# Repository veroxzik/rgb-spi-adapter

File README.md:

# rgb-spi-adapter
 Simple breakout board for the TLC59711 for use with rhythm game controllers.

## Current Release

v1.1 swaps the RGB headers around for compatibility with Yuancon controllers.

## Explanation
Designed for common anode RGBs. Individually wired works just fine too.

- Connectors are JST-XH 4 pin.
- Capacitors are 1uF 0805.
- Resistor is 0805, value per TLC59711 datasheet for your desired current.
- Solder jumper only if you're using 3.3V voltage across the board (LED and logic). Otherwise leave it open for 5V.

Use Adafruit TLC59711 library (get from Arduino library manager). It's plug and play!

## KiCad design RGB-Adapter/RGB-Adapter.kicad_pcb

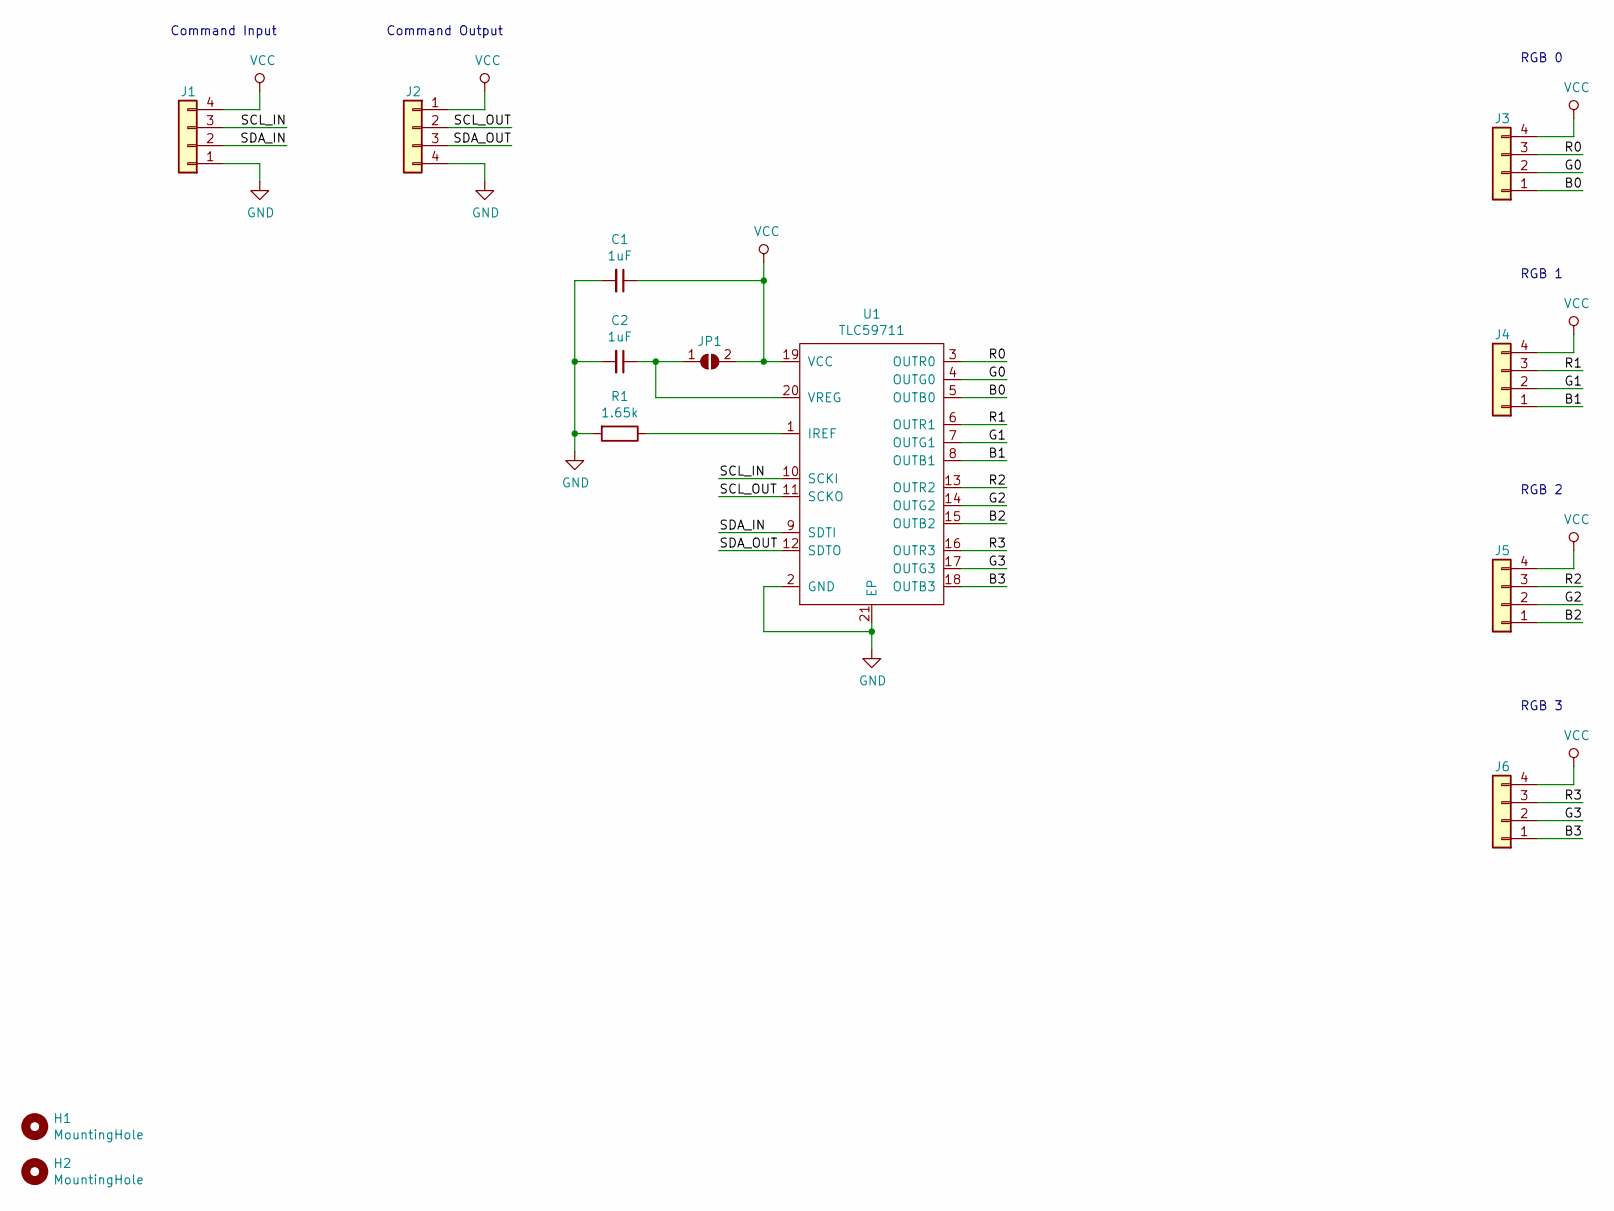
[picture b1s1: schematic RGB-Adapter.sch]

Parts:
C1, C2: 1uF; C_0603_1608Metric_Pad1.05x0.95mm_HandSolder
H1, H2: MountingHole; MountingHole_3.2mm_M3_DIN965
J1, J2, J3, J4, J5, J6: Conn_01x04; JST_XH_B4B-XH-A_1x04_P2.50mm_Vertical
JP1: SolderJumper_2_Open; SolderJumper-2_P1.3mm_Open_RoundedPad1.0x1.5mm
R1: 1.65k; R_0603_1608Metric_Pad1.05x0.95mm_HandSolder
U1: TLC59711; HTSSOP-20-1EP_4.4x6.5mm_P0.65mm_EP3.4x6.5mm_Mask2.75x3.43mm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

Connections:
/B0: J3.1, U1.5 (OUTB0)
/B1: J4.1, U1.8 (OUTB1)
/B2: J5.1, U1.15 (OUTB2)
/B3: J6.1, U1.18 (OUTB3)
/G0: J3.2, U1.4 (OUTG0)
/G1: J4.2, U1.7 (OUTG1)
/G2: J5.2, U1.14 (OUTG2)
/G3: J6.2, U1.17 (OUTG3)
/R0: J3.3, U1.3 (OUTR0)
/R1: J4.3, U1.6 (OUTR1)
/R2: J5.3, U1.13 (OUTR2)
/R3: J6.3, U1.16 (OUTR3)
/SCL_IN: J1.3, U1.10 (SCKI)
/SCL_OUT: J2.2, U1.11 (SCKO)
/SDA_IN: J1.2, U1.9 (SDTI)
/SDA_OUT: J2.3, U1.12 (SDTO)
GND: C1.2, C2.2, J1.1, J2.4, R1.2, U1.2 (GND), U1.21 (EP)
unnamed: C2.1, JP1.1 (A), U1.20 (VREG)
unnamed: R1.1, U1.1 (IREF)
VCC: C1.1, J1.4, J2.1, J3.4, J4.4, J5.4, J6.4, JP1.2 (B), U1.19 (VCC)

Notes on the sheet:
Command Input
RGB 0
Command Output
RGB 1
RGB 2
RGB 3

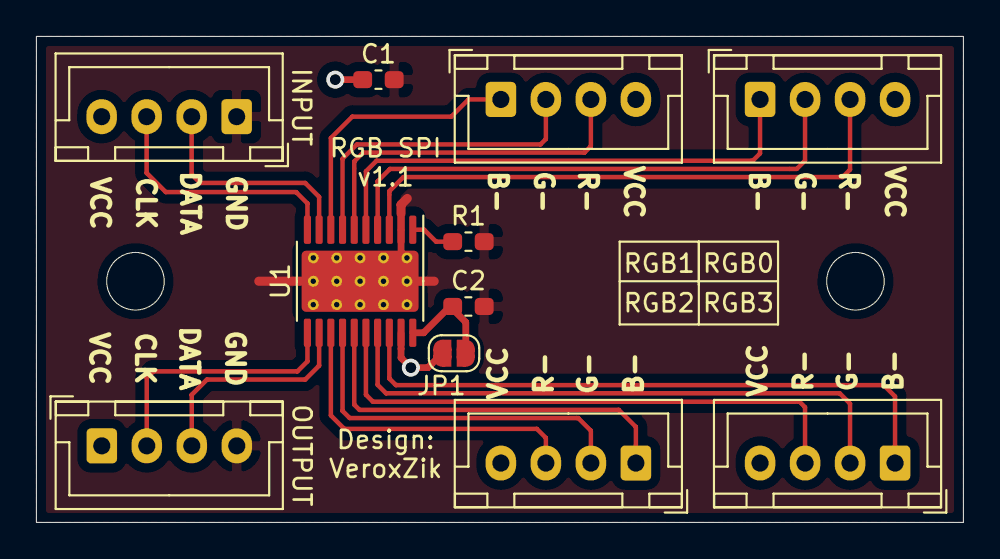
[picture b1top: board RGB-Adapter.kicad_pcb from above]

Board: 2 copper layers, 51.5 x 27.0 mm, 13 parts (0 on the bottom side), 20 nets.

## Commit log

2020-03-21 Initial Commit
    Basic readme, board files!
